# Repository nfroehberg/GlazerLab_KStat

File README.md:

# KStat open source potentiostat

The KStat is an adaptation with small changes to the firmware and PCB design of the open source DStat potentiostat by Michael Dryden for use with Hg/Au microelectrodes in in-situ meaurements.

Documentation for the original design: http://microfluidics.utoronto.ca/gitlab/dstat/dstat-documentation/wikis/home

For the KStat, the potential range of the potentiostat was increased from 3 to 4 (+- 2) V and the shape of the board changed from square to rectangular for easier integration in underwater housings.
As it is intended to be used in conjunction with other sensors and manipulators, the KStat uses a command-line python interface instead of the original GUI. For data analysis, a TKinter GUI was developed to display cyclic voltammograms, fit and/or remove a polynomial baseline, filter out A/C noise and measure peak heights.
Additional scripts include pH measurement and various tests used during the development.

Adaptations to firmware and PCB design by Stanley Lio.

Development of Python Interface by Nico Fröhberg.

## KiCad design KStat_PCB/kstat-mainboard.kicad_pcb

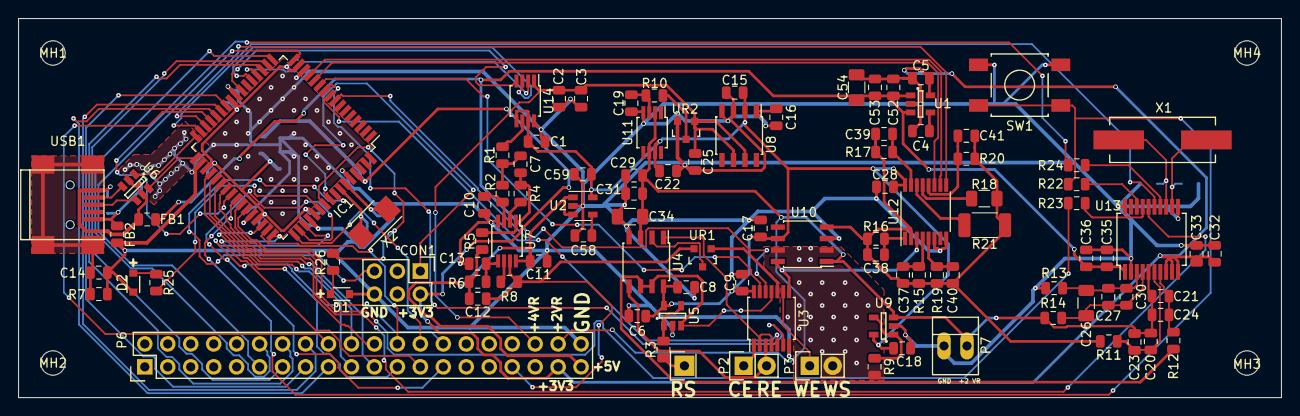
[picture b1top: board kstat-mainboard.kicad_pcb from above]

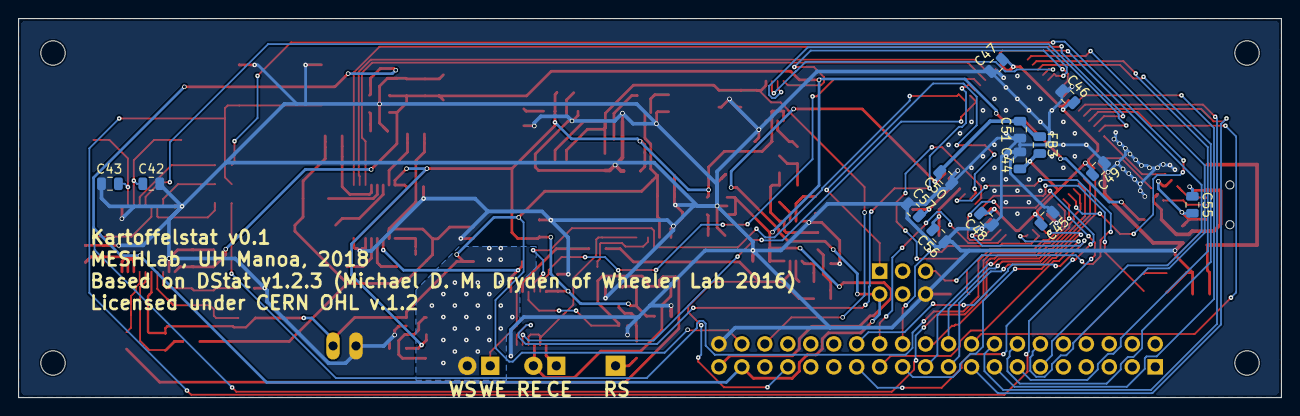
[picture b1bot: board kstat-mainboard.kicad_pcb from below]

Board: 2 copper layers, 139.7 x 41.9 mm, 121 parts (14 on the bottom side), 98 nets.

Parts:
C1, C2, C6, C8, C11, C16, C17, C18, C20, C21, C22, C27, C28, C29, C33, C35, C45, C46, C47, C48, C49, C50, C52: 100n; C_0805_2012Metric
C3, C19, C25, C31, C53: 1u; C_0805_2012Metric
C4, C9, C55, C58: 10n; C_0805_2012Metric
C5, C32, C36, C44, C51, C59: 10u; C_0805_2012Metric
C7, C12: 180p; C_0805_2012Metric
C10: 160p; C_0805_2012Metric
C13: 68p; C_0805_2012Metric
C14, C15: 4.7n; C_0805_2012Metric
C23, C24, C30: 100p; C_0805_2012Metric
C26, C34, C54: 47u; C_1206_3216Metric
C37: 56n; C_0805_2012Metric
C38: 200p; C_0805_2012Metric
C39: 2p; C_0805_2012Metric
C40: 2n; C_0805_2012Metric
C41: 20p; C_0805_2012Metric
C42, C43: 18p; C_0805_2012Metric
C56, C57: 15p; C_0805_2012Metric
CON1: AVR-PDI; Pin_Header_Straight_2x03
D1, D2: LED; D_0805
FB1, FB2: FILTER; C_0805_2012Metric
FB3: FERRITE; C_0805_2012Metric
IC1: ATXMEGA256A3U; TQFP-64_14x14mm_P0.8mm
MH1, MH2, MH3, MH4: MountingHole; MountingHole_2.7mm_M2.5
P1: RS; Pin_Header_Straight_1x01
P2: C R; Pin_Header_Straight_1x02
P3: W WS; Pin_Header_Straight_1x02
P6: CONN_01X40; Pin_Header_Straight_2x20
P7: CONN_2; PINHEAD1-2
R1, R2: 18.7k; R_0805_2012Metric
R3, R9, R15, R22, R23, R24: 100; R_0805_2012Metric
R4, R8: 1k; R_0805_2012Metric
R5, R6: 25.5k; R_0805_2012Metric
R7: 1M; R_0805_2012Metric
R10: 10k; R_0805_2012Metric
R11, R12: 301; R_0805_2012Metric
R13, R14: 49.9; R_0805_2012Metric
R16: 30k; R_0805_2012Metric
R17: 3M; R_0805_2012Metric
R18: 100M; R_1206_3216Metric
R19: 3k; R_0805_2012Metric
R20: 300k; R_0805_2012Metric
R21: 30M; R_2010_5025Metric
R25, R26: 330; R_0805_2012Metric
SW1: RESET; SW_SPST_SMD
U1: TPS79933; SOT-23-5
U2: TPS793475-EP; SOT-23-5
U3: MAX4737; TSSOP-14_4.4x5mm_Pitch0.65mm
U4: LMP7702; SOIC-8_3.9x4.9mm_Pitch1.27mm
U5, U9: LMP7715MF; SOT-23-5
U6: TPD2S017; SOT-23-6
U7: MAX4477; MSOP-8_3x3mm_Pitch0.65mm
U8: MAX6126; SOIC-8_3.9x4.9mm_Pitch1.27mm
U10: LMP7721; SOIC-8_3.9x4.9mm_Pitch1.27mm
U11: OPA350; MSOP-8_3x3mm_Pitch0.65mm
U12: MAX4617; TSSOP-16_4.4x5mm_Pitch0.65mm
U13: ADS1255; SSOP-20_5.3x7.2mm_Pitch0.65mm
U14: MAX5441; MSOP-8_3x3mm_P0.65mm
UR1, UR2: MAX5491; SOT-23
USB1: USB-MB-S; USB_Mini-B
X1: 7.68M; Crystal_HC49-SD_SMD
X2: 12 MHz; Crystal_SMD_5032_2Pads

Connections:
+2VR: C20.1, C21.1, C23.1, C24.1, C29.1, C31.1, C34.1, P6.38, P7.2, R14.1, U4.3, U9.3, U10.1, U11.2, U11.6, U13.5
+3V3: C5.2, C32.2, C33.2, C50.2, C51.2, CON1.2, FB3.2, IC1.61, P6.37, U1.5, U13.8, U13.9, U13.10
+4.75VR: C1.1, C6.1, C8.1, C9.2, C15.1, C17.2, C18.1, C22.1, C28.2, C59.1, U2.5, U3.14, U4.8, U5.5, U8.2, U9.5, U10.6, U11.7, U12.16, U14.5, U14.7
+4VR: C2.1, C3.1, C25.1, P6.36, U8.6, U8.7, U14.1, UR2.1
+5V: C11.1, C35.1, C36.1, C52.1, C53.1, C54.1, FB1.1, P6.39, U1.1, U1.3, U2.1, U2.3, U7.8, U13.1
/ADC: C37.2, C38.2, C39.2, C40.2, C41.2, R11.1, R15.2, R16.2, R17.2, R18.2, R19.2, R20.2, R21.2, U10.4, U12.2
/COUNTER: P2.1, U3.1
/DAC_OUT: C12.2, P6.33, R8.1, U7.7, UR1.2
/DM: IC1.32, U6.1
/DP: IC1.33, U6.6
/PB2: IC1.8, U3.12
/PB3: IC1.9, U3.5
/PB4: IC1.10, U3.6
/PB5: IC1.11, U3.13
/PB6: IC1.12, U12.11
/PB7: IC1.13, U12.10
/PC0: IC1.16, P6.11
/PC1: IC1.17, P6.12
/PC2: IC1.18, P6.13
/PC3: IC1.19, P6.14
/PC4: IC1.20, U14.2
/PC5: IC1.21, U14.3
/PC7: IC1.23, U14.4
/PD0: IC1.26, P6.15
/PD1: IC1.27, P6.16
/PD2: IC1.28, P6.17
/PD3: IC1.29, P6.18
/PD4: IC1.30, U12.9
/PD5: IC1.31, U13.15
/PDI_CLK: CON1.5, IC1.57
/PDI_DATA: CON1.1, IC1.56
/PE0: IC1.36, P6.19
/PE1: IC1.37, P6.20
/PE2: IC1.38, P6.21
/PE3: IC1.39, P6.22
/PE4: IC1.40, R24.2
/PE5: IC1.41, R22.2, SW1.1
/PE6: IC1.42, U13.16
/PE7: IC1.43, R23.2
/PF0: IC1.46, P6.23
/PF1: IC1.47, P6.24
/PF2: IC1.48, P6.25
/PF3: IC1.49, P6.26
/PF4: IC1.50, P6.27
/PF5: IC1.51, P6.28
/PF6: IC1.54, R25.1
/PF7: IC1.55, R26.1
/REFERENCE: P2.2, U3.3, U4.5
/REF_V: R12.1, U3.11, U4.6, U4.7, U5.3
/RSHIELD: P1.1, R3.2
/USB_GND: C55.2, FB2.2, U6.2, USB1.5
/USB_VCC: C55.1, FB1.2, U6.5, USB1.1
/WORKING: P3.1, U3.9
/WSHIELD: P3.2, R9.2, U10.2, U10.7
GND: C1.2, C2.2, C3.2, C4.2, C5.1, C6.2, C8.2, C9.1, C10.1, C11.2, C13.1, C14.2, C15.2, C16.2, C17.1, C18.2, C19.2, C22.2, C25.2, C28.1, C29.2, C31.2, C32.1, C33.1, C34.2, C35.2, C36.2, C42.2, C43.2, C44.1, C45.1, C46.1, C47.1, C48.1, C49.1, C50.1, C51.1, C52.2, C53.2, C54.2, C56.1, C57.1, C58.2, C59.2, CON1.6, D1.1, D2.1, FB2.1, IC1.14, IC1.24, IC1.34, IC1.44, IC1.52, IC1.60, P6.40, P7.1, R7.2, R13.1, SW1.2, U1.2, U2.2, U3.7, U4.4, U5.2, U7.4, U8.3, U8.4, U9.2, U10.3, U11.4, U12.6, U12.8, U13.2, U13.11, U13.20, U14.8, UR2.2
unnamed: C4.1, U1.4
unnamed: C7.1, R1.2, R2.1
unnamed: C7.2, R4.1, R5.1, U7.1
unnamed: C10.2, R2.2, U7.3
unnamed: C12.1, R5.2, R6.1
unnamed: C13.2, R6.2, U7.5
unnamed: C14.1, R7.1, USB1.6
unnamed: C16.1, U8.1
unnamed: C19.1, R10.2, U11.3
unnamed: C20.2, C23.2, R11.2, U13.6
unnamed: C21.2, C24.2, R12.2, U13.7
unnamed: C26.1, C27.1, C30.1, R13.2, U13.3
unnamed: C26.2, C27.2, C30.2, R14.2, U13.4
unnamed: C37.1, R15.1, U12.4
unnamed: C38.1, R16.1, U12.1
unnamed: C39.1, R17.1, U12.15
unnamed: C40.1, R19.1, U12.5
unnamed: C41.1, R20.1, U12.12
unnamed: C42.1, U13.13, X1.2
unnamed: C43.1, U13.12, X1.1
unnamed: C44.2, C45.2, C46.2, C47.2, C48.2, C49.2, FB3.1, IC1.15, IC1.25, IC1.35, IC1.45, IC1.53
unnamed: C56.2, IC1.58, X2.2
unnamed: C57.2, IC1.59, X2.1
unnamed: C58.1, U2.4
unnamed: D1.2, R26.2
unnamed: D2.2, R25.2
unnamed: R1.1, U14.6
unnamed: R3.1, U5.1, U5.4
unnamed: R4.2, U7.2
unnamed: R8.2, U7.6
unnamed: R9.1, U9.1, U9.4
unnamed: R10.1, UR2.3
unnamed: R18.1, U12.13
unnamed: R21.1, U12.14
unnamed: R22.1, U13.18
unnamed: R23.1, U13.17
unnamed: R24.1, U13.14
unnamed: U3.2, U3.4, U4.1
unnamed: U3.10, UR1.1
unnamed: U4.2, UR1.3
unnamed: U6.3, USB1.2
unnamed: U6.4, USB1.3
unnamed: U3.8, U10.8, U12.3

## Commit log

2019-05-14 Initializing Git Repository
2019-05-14 Adding Python Scripts
2019-05-14 Editing the readme
2019-05-15 Updating Readme
2019-05-15 adding scripts for in-situ and sediment work
2019-05-15 change folder name

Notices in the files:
KStat_PCB/kstat-mainboard.kicad_pcb:
©Michael D. M. Dryden 2016
This documentation describes Open Hardware and is licensed under the CERN OHL v. 1.2.
Licensed under CERN OHL v.1.2
You may redistribute and modify this documentation under the terms of the CERN OHL v.1.2. (http://ohwr.org/cernohl).
